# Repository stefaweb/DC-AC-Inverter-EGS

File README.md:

# Mini DC-AC-Inverter-EGS 1.0.2

PCB size: 90x44mm

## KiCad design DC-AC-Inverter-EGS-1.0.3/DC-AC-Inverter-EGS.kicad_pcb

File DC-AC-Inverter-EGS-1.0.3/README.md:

# Mini DC-AC-Inverter-EGS 1.0.3

PCB size: 90x44mm

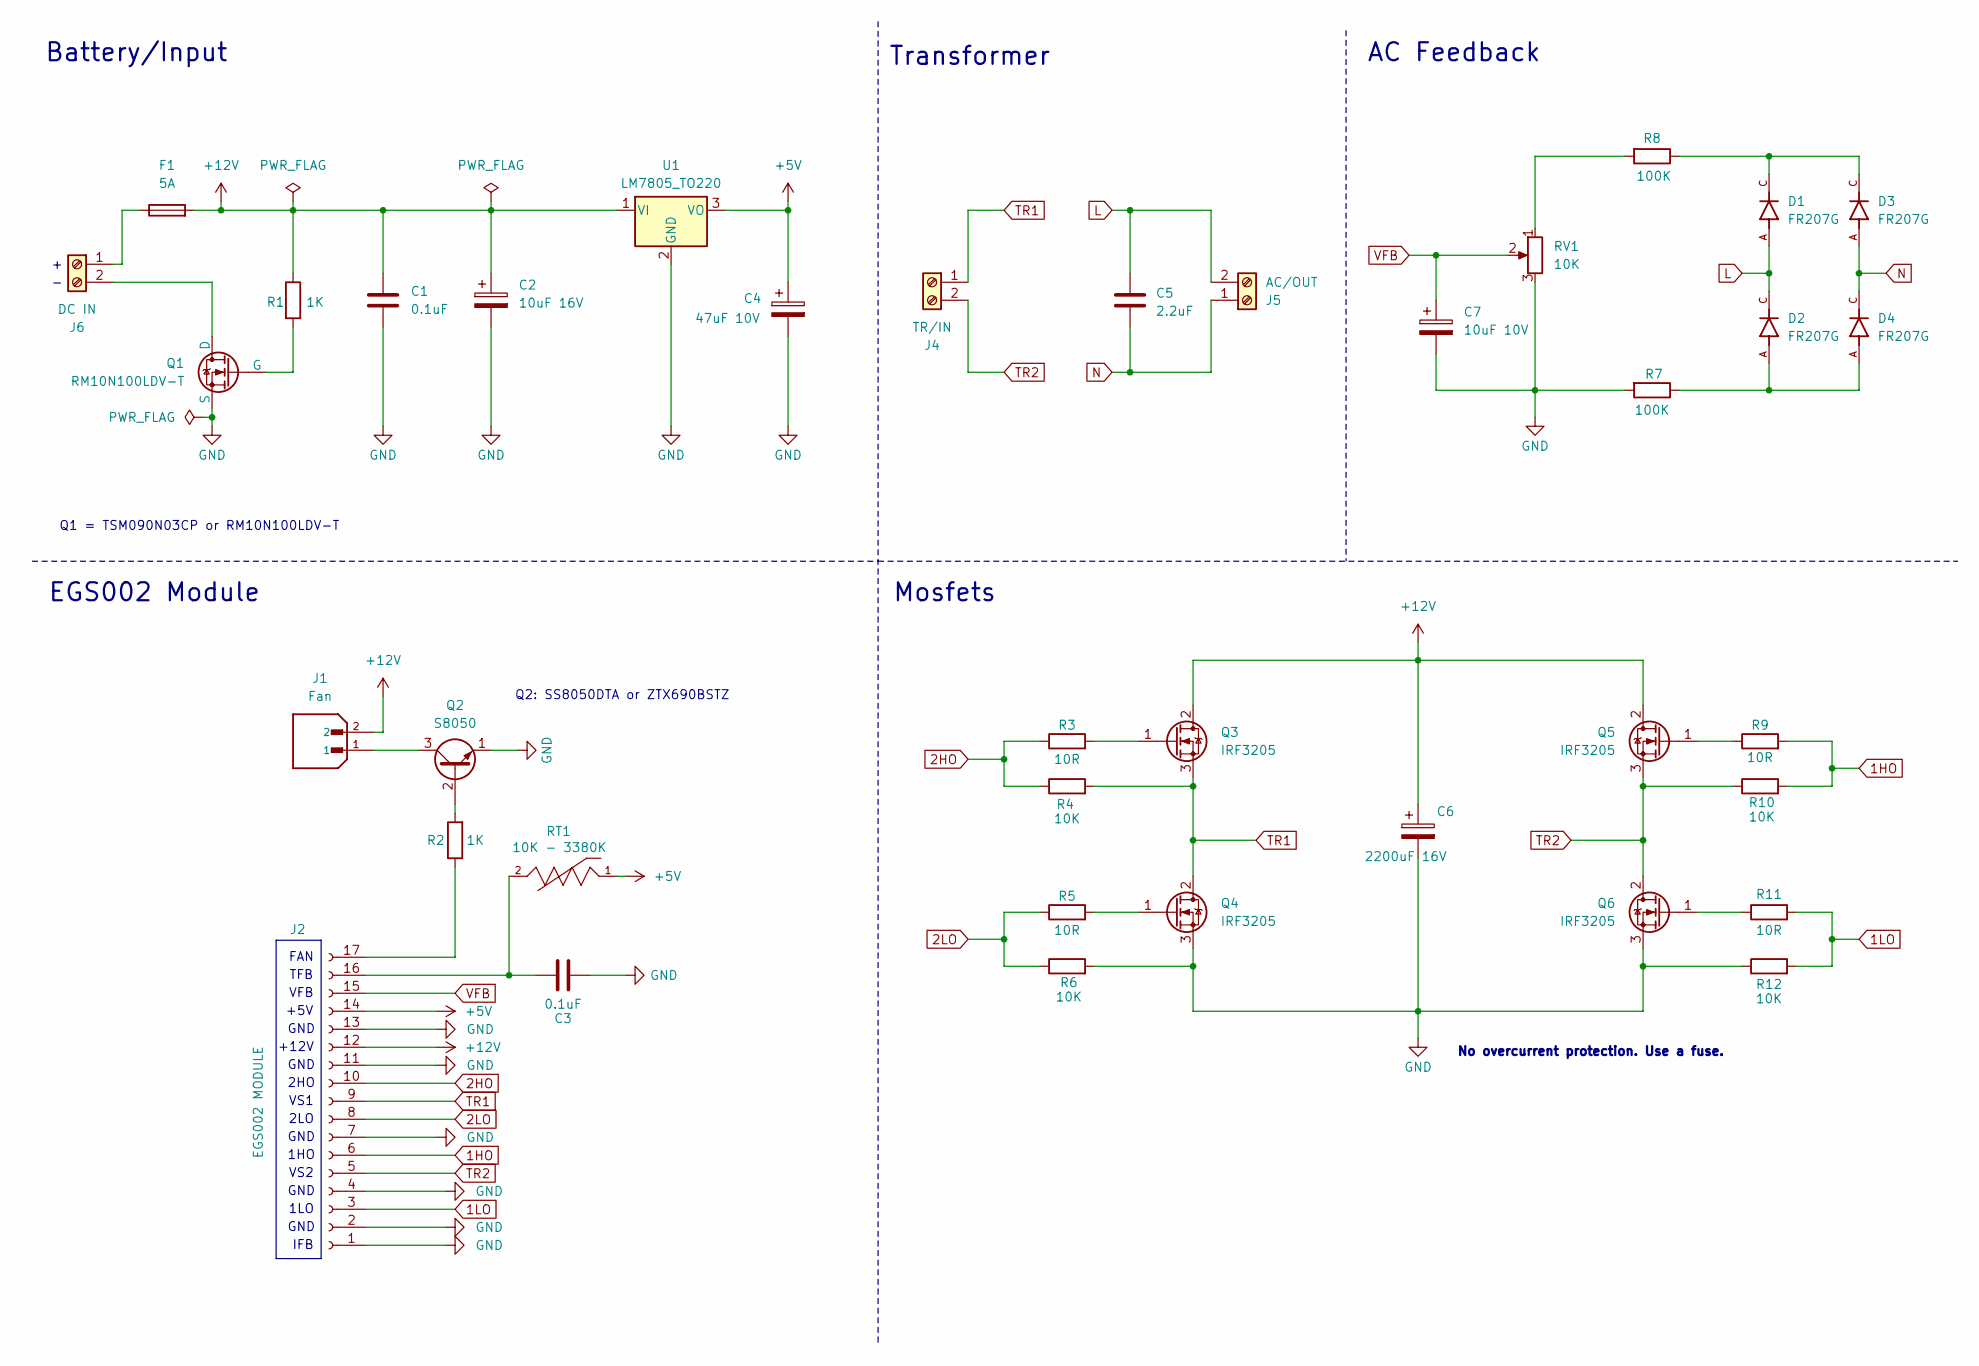
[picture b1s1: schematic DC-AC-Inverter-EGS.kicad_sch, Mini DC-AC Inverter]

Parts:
C1, C3: 0.1uF; C_Rect_L7.2mm_W2.5mm_P5.00mm_FKS2_FKP2_MKS2_MKP2
C2: 10uF 16V; CP_Radial_D5.0mm_P2.50mm
C4: 47uF 10V; CP_Radial_D5.0mm_P2.50mm
C5: 2.2uF; C_Rect_L18.0mm_W8.0mm_P15.00mm_FKS3_FKP3; Part# MKS4D042204F00KSSD; Mouser 505-MKS4D042204FKSSD
C6: 2200uF 16V; CP_Radial_D12.5mm_P5.00mm
C7: 10uF 10V; CP_Radial_D5.0mm_P2.50mm
D1, D2, D3: FR207G; PARTREV F2105; Mouser 821-FR207G
D4: FR207G; Part# FR207G; Mouser 821-FR207G
F1: 5A; Fuse_Littelfuse_372_D8.50mm
J1: Fan; JST_XH_B2B-XH-A_1x02_P2.50mm_Vertical; PARTREV N/A
J2: EGS002 MODULE; PinSocket_1x17_P2.54mm_Vertical
J4: TR/IN; TerminalBlock_Phoenix_PT-1,5-2-5.0-H_1x02_P5.00mm_Horizonta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
J5: AC/OUT; TerminalBlock_Phoenix_PT-1,5-2-5.0-H_1x02_P5.00mm_Horizonta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
J6: DC IN; TerminalBlock_Phoenix_PT-1,5-2-5.0-H_1x02_P5.00mm_Horizonta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
Q1: RM10N100LDV-T; TO-252-3_TabPin2; Part# RD3P03BBHTL1; Mouser 755-RD3P03BBHTL1
Q2: S8050; TO-92_Inline_Wide; Part# SS8050DTA; Mouser 512-SS8050DTA
Q3, Q4, Q5, Q6: IRF3205; TO-220-3_Vertical; Part# IRF3205PBF; Mouser 942-IRF3205PBF
R1: 1K; R_Axial_DIN0207_L6.3mm_D2.5mm_P2.54mm_Vertical
R2: 1K; R_Axial_DIN0207_L6.3mm_D2.5mm_P10.16mm_Horizontal
R3, R5, R9, R11: 10R; R_Axial_DIN0207_L6.3mm_D2.5mm_P10.16mm_Horizontal
R4, R6, R10, R12: 10K; R_Axial_DIN0207_L6.3mm_D2.5mm_P10.16mm_Horizontal
R7, R8: 100K; R_Axial_DIN0207_L6.3mm_D2.5mm_P10.16mm_Horizontal
RT1: 10K - 3380K; THERM_NXRT15WB333JA3A016; PARTREV N/A
RV1: 10K; Potentiometer_Bourns_3296W_Vertical
U1: LM7805_TO220; TO-220-3_Vertical; Part# LM7805CT/NOPB; Mouser 926-LM7805CT/NOPB

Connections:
1HO: J2.6, R9.2, R10.2
1LO: J2.3, R11.2, R12.2
2HO: J2.10, R3.1, R4.1
2LO: J2.8, R5.1, R6.1
+5V: C4.1, J2.14, RT1.1, U1.3 (VO)
+12V: C1.1, C2.1, C6.1, F1.2, J1.2, J2.12, Q3.2 (D), Q5.2 (D), R1.1, U1.1 (VI)
GND: C1.2, C2.2, C3.2, C4.2, C6.2, C7.2, J2.1, J2.2, J2.4, J2.7, J2.11, J2.13, Q1.3 (S), Q2.1 (E), Q4.3 (S), Q6.3 (S), R6.2, R7.2, R12.1, RV1.3, U1.2 (GND)
L: C5.1, D1.A, D2.C, J5.2
N: C5.2, D3.A, D4.C, J5.1
unnamed: D1.C, D3.C, R8.1
unnamed: D2.A, D4.A, R7.1
unnamed: C3.1, J2.16, RT1.2
unnamed: J2.17, R2.1
unnamed: F1.1, J6.1
unnamed: J6.2, Q1.1 (D)
unnamed: Q1.2 (G), R1.2
unnamed: Q2.2 (B), R2.2
unnamed: J1.1, Q2.3 (C)
unnamed: Q3.1 (G), R3.2
unnamed: Q4.1 (G), R5.2
unnamed: Q5.1 (G), R9.1
unnamed: Q6.1 (G), R11.1
unnamed: R8.2, RV1.1
TR1: J2.9, J4.1, Q3.3 (S), Q4.2 (D), R4.2
TR2: J2.5, J4.2, Q5.3 (S), Q6.2 (D), R10.1
VFB: C7.1, J2.15, RV1.2

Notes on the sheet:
VFB
VS2
GND
No overcurrent protection. Use a fuse.
2HO
Battery/Input
Q2: SS8050DTA or ZTX690BSTZ
Q1 = TSM090N03CP or RM10N100LDV-T
EGS002 Module
1HO
1LO
TFB
IFB
VS1
Transformer
AC Feedback
2LO
+5V
FAN
+12V
Mosfets

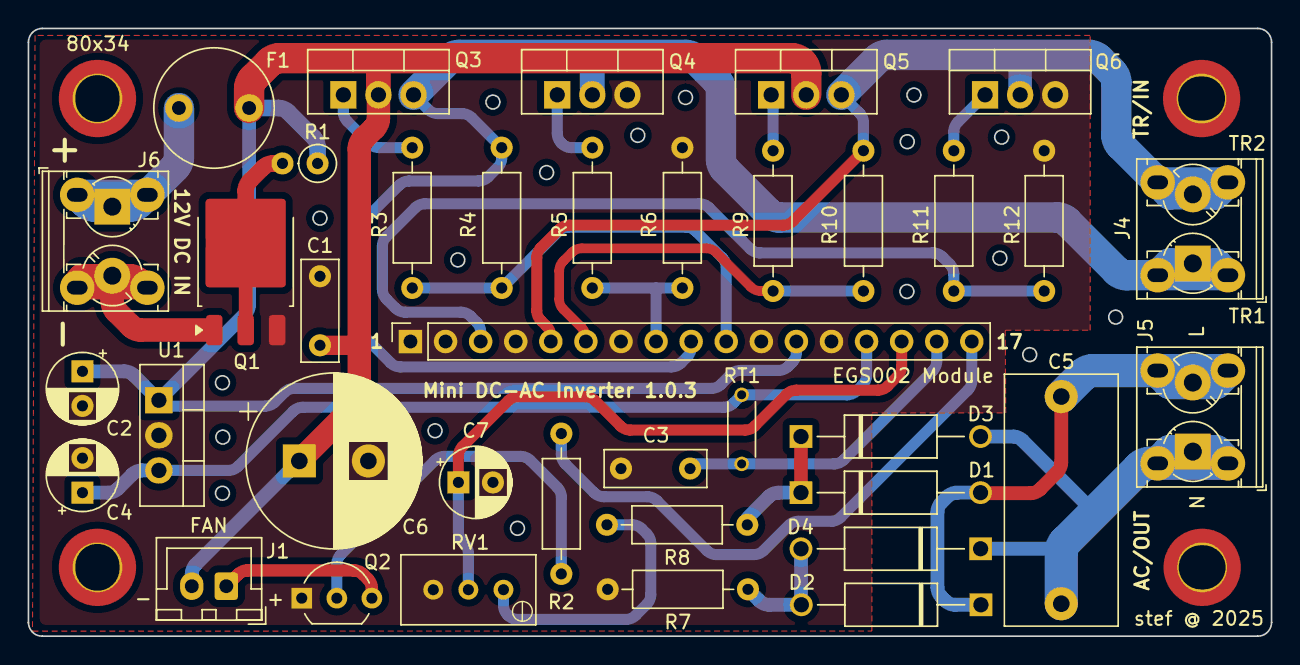
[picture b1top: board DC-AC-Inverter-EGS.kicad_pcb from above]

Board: 2 copper layers, 90.0 x 44.0 mm, 42 parts (0 on the bottom side), 26 nets.

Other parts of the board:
H1, H1#2, H1#3, H1#4: MountingHole; MountingHole_3.2mm_M3_DIN965_Pad_TopBottom

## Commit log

2025-01-21 First upload
2025-01-24 Update folder
2025-02-25 Upload DC-AC-Inverter-EGS-1.0.3
